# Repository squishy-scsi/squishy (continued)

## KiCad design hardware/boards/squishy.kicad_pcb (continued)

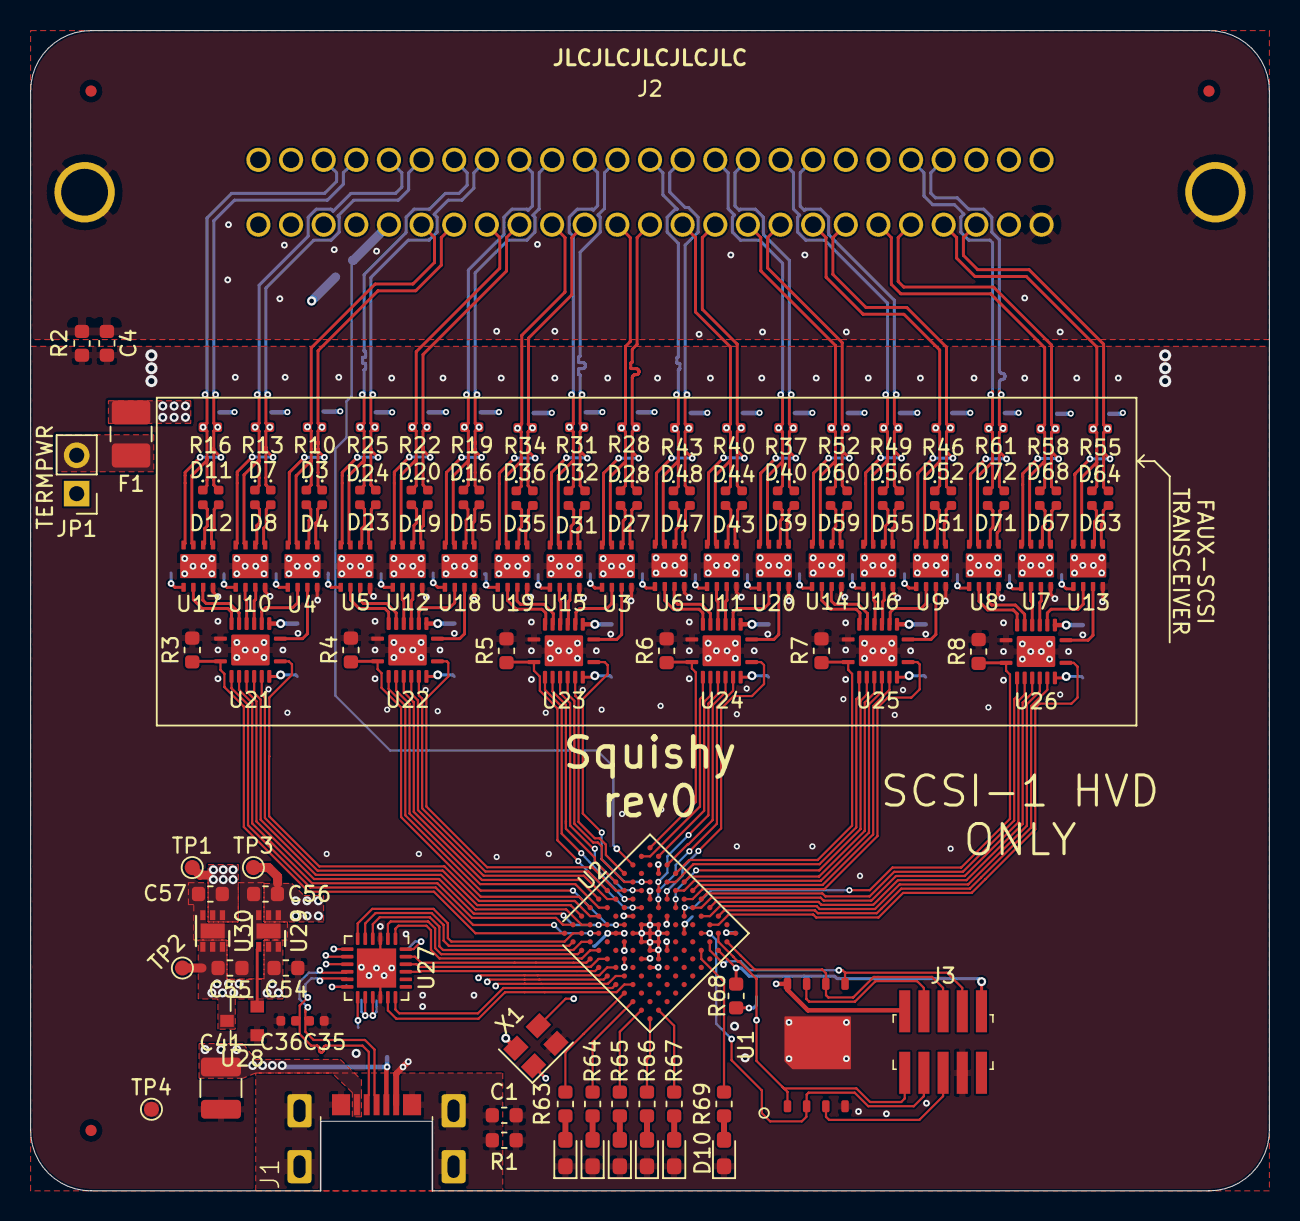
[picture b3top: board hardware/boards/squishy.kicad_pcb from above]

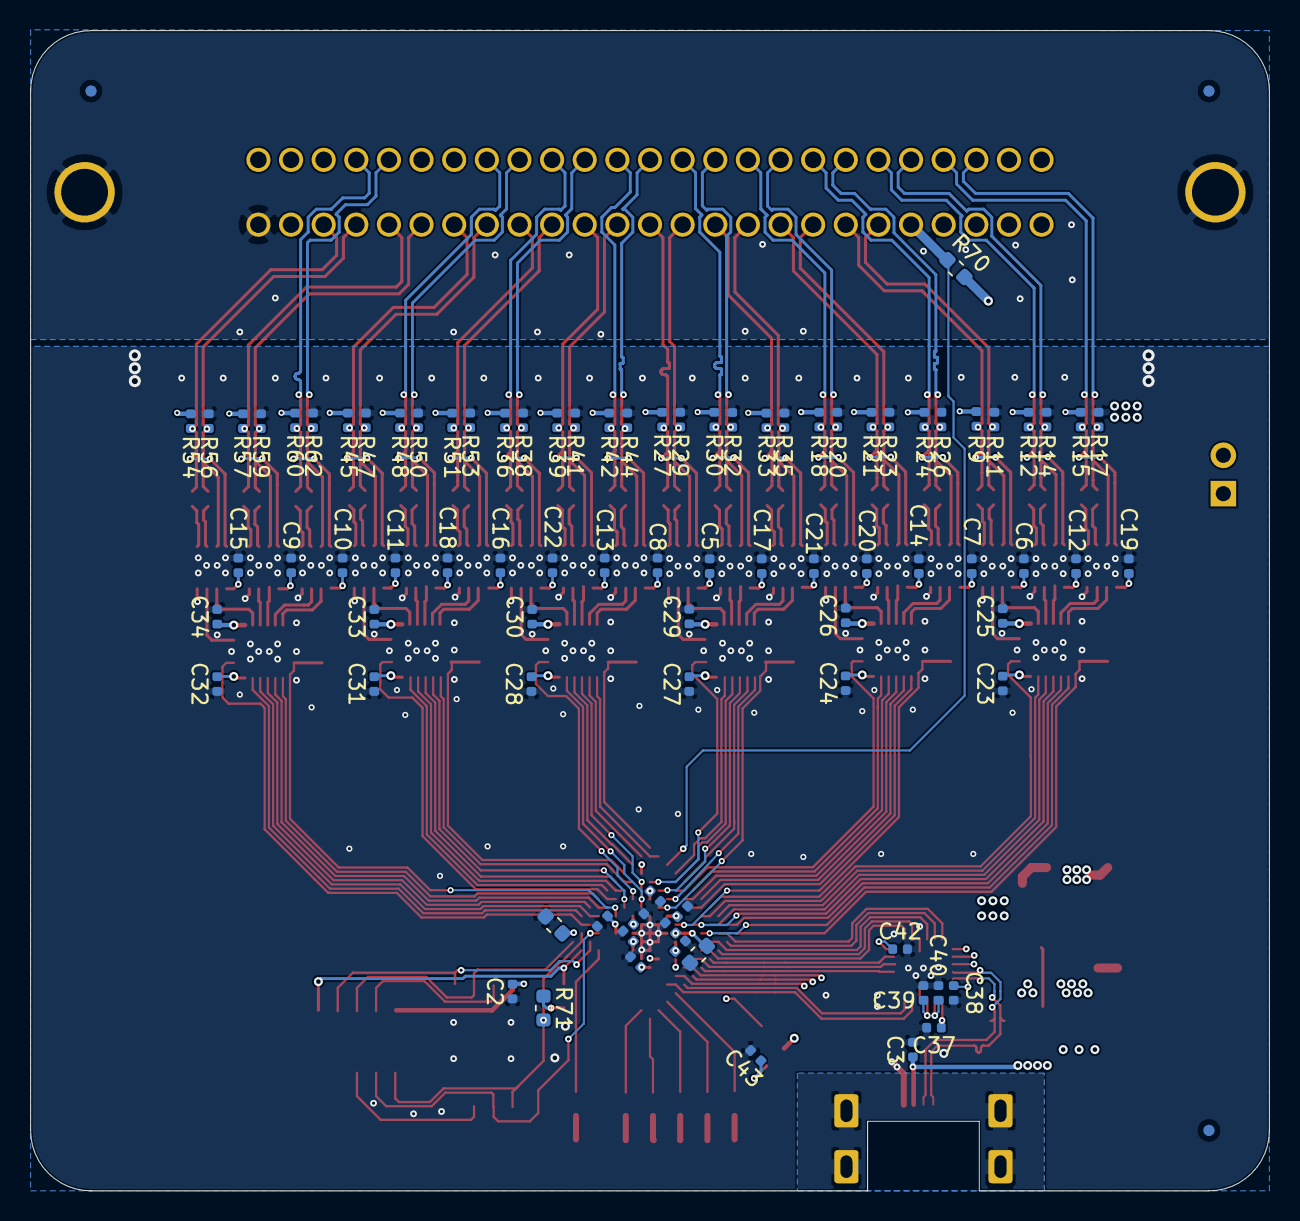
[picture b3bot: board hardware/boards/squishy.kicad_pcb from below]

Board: 4 copper layers, 82.0 x 76.8 mm, 216 parts (89 on the bottom side), 196 nets.

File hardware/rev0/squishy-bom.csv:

Reference,Quantity,Value,Datasheet,MFR,MPN
C1 C4,2,0.1uF,~,KEMET,C0603C104M5RACTU
C18 C17 C12 C6 C20 C14 C8 C22 C16 C10 C11 C5 C19 C13 C7 C21 C15 C9 C24 C26 C23 C25 C28 C30 C27 C29 C32 C34 C31 C33 C2 C42 C37 C38 C39 C40 C48 C50 C52 C46 C49 C51 C53 C47,44,0.1uF,~,KEMET,C0402C104M8PACTU
C3 C43,2,0.01uF,~,KEMET,C0402C103K3RACTU
C35 C36,2,47pf,~,KEMET,C0402C470K5GACTU
C41,1,100uF,~,KEMET,C1210C107M4PAC7800
C44 C45 C56 C54 C57 C55,6,4.7uF,~,KEMET,C0603C475K8PACTU
D1 D9 D10,3,BLUE,~,Wurth Electronics,150060BS75000
D2 D6,2,PINK,~,Optosupply,OSK40603C1E
D35 D36 D59 D60 D11 D12 D15 D16 D19 D20 D31 D32 D55 D56 D7 D8 D63 D64 D43 D44 D23 D24 D47 D48 D51 D52 D27 D28 D3 D4 D72 D71 D68 D67 D40 D39,36,D_Schottky_Small,https://www.comchiptech.com/admin/files/product/CDBQR0230L-H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,Comchip,CDBQR0230L-HF
D5,1,WHITE,~,ROHM Semiconductor,SMLEN3WBC8W1
F1,1,Polyfuse_Small,~,Bel Fuse,0ZCH0050FF2G
J1,1,USB_B_Micro,https://cdn.amphenol-icc.com/media/wysiwyg/files/drawing/101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,Amphenol ICC,10103593-0001lf
J2,1,Conn_02x26_Top_Bottom,https://content.norcomp.net/rohspdfs/SCSI-050Ribbon/11Y/112/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,NorComp,112-050-113R001
J3,1,Conn_02x05_Odd_Even,~,Samtec,FTSH-105-01-L-DV-K-TR
R1 R2,2,1M,~,Vishay Dale,CRCW06031M00FKEA
R4 R3 R6 R5 R8 R7 R66 R64 R70 R71 R68,11,10k,~,Vishay Dale,CRCW060310K0FKEA
R45 R47 R48 R50 R51 R53 R54 R56 R57 R59 R60 R62 R27 R29 R30 R32 R33 R35 R36 R38 R39 R41 R42 R44 R9 R11 R12 R14 R15 R17 R18 R20 R21 R23 R24 R26,36,330,~,TE Connectivity Passive Product ,CRGCQ0402F330R
R46 R49 R52 R55 R58 R61 R28 R31 R34 R37 R40 R43 R10 R13 R16 R19 R22 R25,18,150,~,TE Connectivity Passive Product ,CRGCQ0402F150R
R65,1,6k8,~,Vishay Dale,CRCW06036K80FKEA
R67 R63 R69,3,4k7,~,Vishay Dale,CRCW06034K70FKEA
U1,1,128MiB,https://www.winbond.com/resource-files/w25n01gv%20revl%20050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,Winbond,W25N01GVZEIG TR
U2,1,ICE40HX8K-BG121,http://www.latticesemi.com/Products/FPGAandCPLD/iCE40,Lattice Semiconductors,ICE40HX8K-BG121
U22 U21 U24 U23 U26 U25,6,TXB0106,https://www.ti.com/lit/ds/symlink/txb0106.pdf?HQS=TI-null-nu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,Texas Instruments,TXB0106RGYR
U27,1,FT240XQ,https://www.ftdichip.com/Support/Documents/DataSheets/ICs/DS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,FTDI,FT240XQ-R
U28,1,MAX809JTRG,https://www.mouser.com/datasheet/2/308/MAX809S-D-1811035.pdf,ON Semiconductors,MAX809JTRG
U29,1,TLV755533PDRVR,http://www.ti.com/lit/ds/symlink/tlv733p-q1.pdf,Texas Instruments,TLV75533PDRVR
U30,1,TLV73312PQDRVRQ1,http://www.ti.com/lit/ds/symlink/tlv755p.pdf,Texas Instruments,TLV73312PQDRVRQ1
U4 U7 U6 U13 U8 U19 U5 U11 U17 U3 U9 U15 U14 U20 U12 U18 U10 U16,18,THVD1451,https://www.ti.com/lit/ds/symlink/thvd1410.pdf?HQS=TI-null-n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,Texas Instruments,THVD1451DRBR
X1,1,ASEM-48MHz,http://abracon.com/Oscillators/ASEMB.pdf,Abracon,ASEMB-48.000MHZ-LY-T

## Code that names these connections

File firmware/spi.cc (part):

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	PORTA.set_output(pin::PSRAM_CS);

	/* Set up FPGA SPI Bus */
	PORTA.set_high(pin::FPGA_CS);
	PORTA.set_output(pin::FPGA_CS);

	PORTA.set_low(pin::FPGA_CLK);
	PORTA.set_output(pin::FPGA_CLK);

	PORTA.set_low(pin::FPGA_COPI);
	PORTA.set_output(pin::FPGA_COPI);
	PORTA.setup_pin(pin::FPGA_CIPO, false, true, false, false, port_t::pin_func_t::A);
	PORTA.set_input(pin::FPGA_CIPO);
}

static void setup_flash_pins() noexcept {
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static void fpga_begin_cmd(const fpga_cmd_t command) noexcept {
	const auto cmd{static_cast<std::uint8_t>(command)};

	PORTA.set_low(pin::FPGA_CS);

	[[maybe_unused]]
	auto _{fpga_xfr(cmd)};
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
static void fpga_cmd_run(const fpga_cmd_t command) noexcept {
	fpga_begin_cmd(command);
	PORTA.set_high(pin::FPGA_CS);
}

static void fpga_cmd_read(const fpga_cmd_t command, std::span<std::uint8_t> data) noexcept {
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		byte = fpga_xfr();
	}

	PORTA.set_high(pin::FPGA_CS);
}

static void fpga_cmd_write(const fpga_cmd_t command, const std::span<std::uint8_t>& data) noexcept {
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		auto _{fpga_xfr(byte)};
	}

	PORTA.set_high(pin::FPGA_CS);
}


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	for (std::size_t bit{}; bit < 8U; ++bit) {
		PORTA.set_low(pin::FPGA_CLK);

		PORTA.set_value((data >> (7U - bit)) & 0b1, pin::FPGA_COPI);

		/* High tech delay */
		asm (R"(
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
		PORTA.set_high(pin::FPGA_CLK);

		res |= std::uint8_t(PORTA.pin_state(pin::FPGA_CIPO) << (7U - bit));
	}

	PORTA.set_low(pin::FPGA_CLK);
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	for (std::size_t bit{}; bit < 8U; ++bit) {
		PORTA.set_low(pin::FPGA_CLK);

		PORTA.set_value((data >> bit) & 0b1, pin::FPGA_COPI);

		/* High tech delay */
		asm (R"(
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
		PORTA.set_high(pin::FPGA_CLK);

		res |= std::uint8_t(PORTA.pin_state(pin::FPGA_CIPO) << bit);
	}

	PORTA.set_low(pin::FPGA_CLK);
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		return false;
	}

	if (!PORTA.pin_state(pin::FPGA_INIT)) {
		active_fault = fault_code_t::FPGA_CFG_FAILED;
		return false;
	}
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
	/* Ensure the FPGA is released from the hold */
	PORTA.set_high(pin::FPGA_HOLD);
	PORTA.set_low(pin::FPGA_CS);

	if (!fpga_program_status() ) {
		return false;
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
	fpga_cmd_run(fpga_cmd_t::DISABLE);

	if (!PORTA.pin_state(pin::FPGA_DONE)) {
		active_fault = fault_code_t::FPGA_CFG_FAILED;
		return false;
	}
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	const auto bit_len{slot_header.bitstream_len()};

	/* Check if the FPGA is in configuration mode, if not, bail */
	if (PORTA.pin_state(pin::FPGA_DONE) || !PORTA.pin_state(pin::FPGA_INIT)) {
		active_fault = fault_code_t::FPGA_CFG_INVALID;
		return false;
	}
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
	};

	PORTA.set_high(pin::FPGA_CS);

	if (!fpga_program_status() ) {
		return false;
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
	fpga_cmd_run(fpga_cmd_t::DISABLE);

	if (!PORTA.pin_state(pin::FPGA_DONE)) {
		active_fault = fault_code_t::FPGA_CFG_FAILED;
		return false;
	}
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[[nodiscard]]
std::uint8_t read_squishy_register(const std::uint8_t addr) noexcept {

	PORTA.set_low(pin::FPGA_CS);
	[[maybe_unused]]
	auto _{gateware_xfr(addr)};

	const auto val{gateware_xfr(0U)};

	PORTA.set_high(pin::FPGA_CS);

	return val;
}

void write_squishy_register(const std::uint8_t addr, const std::uint8_t val) noexcept {
	PORTA.set_low(pin::FPGA_CS);

	[[maybe_unused]]
	auto _{gateware_xfr(addr)};
	_ = gateware_xfr(val);

	PORTA.set_high(pin::FPGA_CS);
}

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
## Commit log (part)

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2024-10-25 firmware: peripherals: Stubbed out `SYSCTRL` register block
2024-10-25 firmware: memory: Added memory header so we can call `memcpy` et. al.
2024-10-25 firmware: renamed `load_bitstream` to `load_bitstream_flash`
2024-10-25 firmware: spi: Added `fpga_segmented_xfer` to allow for fragmented bitstream loading from PSRAM to FPGA
2024-10-29 firmware: Added a *really* rough readme for building the firmware
2024-11-10 docs: Created connector and pinout diagrams and tables
2024-11-10 docs: pinouts: updated sources list to include direct links to the HD50/HD68 and added the CE50
2024-11-10 docs: pinouts: De-duplicated the SCSI-3 68-pin pinout tables
2024-11-10 docs: pinouts: Updated the scsi-se-50 pinout file
2024-11-10 docs: pinouts: Added the scsi-hvd-68 pinout file
2024-11-10 docs: pinouts: Added the scsi-lvd-68 pinout file
2024-11-18 squishy: gateware: peripherals: Updated SPI Flash peripheral.
    Updated the SPI Flash controller peripheral to use the new SPIController interface, meaning we no longer pass the resource down, we now manually extract the needed subsignals to construct the control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
    NOTE: There is some weirdness with the tests that was fixed by reaching into the SPI controller for it's Bus signals rather than using the global record signals, this reeks of unsoundness, and needs 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
2024-11-18 squishy: gateware: peripherals: Added SPI Interface
    Added a `SPIInterface` module that allows for a single SPI bus resource to be used as both a `SPIController` and/or a `SPIPeripheral` depending on the `SPIInterfaceMode` flag option.
    This is mainly useful for the rev2 platform where we need to act as a peripheral to the supervisor and a controller to the PSRAM that are both on the same SPI bus
2024-11-19 tests: gateware: peripheral: stubbed out the DUT and the test runner for the SPIPeripheral tests
2024-11-19 squishy: gateware: bootloader: started filling in the bits for the Rev2 bootloader
2024-11-20 setup: Bumped Torii version to 0.7.1 as the minimal required version
2024-11-22 squishy: gateware: peripherals: Started de-coupling the SPI XFR from the clock
2024-11-22 tests: gateware: peripherals: Started adding the CPOL Low tests and slowly working the kinks out
2024-11-28 tests: gateware: peripherals: fixed the SPI tests
2024-11-29 gateware: peripherals: spi: Fixed the SPIPeripheral and also filled out the tests
2024-11-29 gateware: peripherals: psram: Started implementing PSRAM read
2024-12-01 gateware: peripherals: psram: actually implemented the `ready` signal, oops
2024-12-01 ci: Updated python version 3.14 and also ensured that if the 3.14 test fails it's okay
2024-12-01 test: peripherals: psram: shrunk the PSRAM data test if we are running in CI so we don't take literally forever
2024-12-03 gateware: bootloader: Removed the unneeded extra addition of the `StallOnlyRequestHandler` as that is built by SOL on-the-fly from handler conditions.
    This also resolved the issue where the bootloader module when provided with the same synth options would fail cache lookup, because the SOL request handler name disambiguation would kick in, this mig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
2024-12-12 core/contrib: Almost fully re-wrote the pcapng generator to make it less awful
2024-12-14 gateware: peripherals: spi: Fixed an potential edge case where CS may drop if we are in the middle of our state machine, causing a de-sync
2024-12-14 gateware: actions: run_synth: was silly and mixed up `>` and `<` again, so it was setting random seed if you ever specified a non-zero PnR seed
2024-12-14 gateware: bootloader: rev2: Actually stuck the SPIPSRAM block into the bootloader for use (RIP our timings, but I guess 175MHz isn't /too/ bad)
2024-12-17 gateware: bootloader: rev2: removed unended aliases for SPI controller and peripheral
2024-12-18 docs: minor updates
2024-12-18 actions: Added a little more info for when the bitstream cache is hit and we're using that
2024-12-18 core/applets: Added initial `LINKTYPE_PARALLEL_SCSI` bits
2024-12-18 core: pcapng: got rid of `if __name__ == '__main__'` from the bottom of the pcapng module that was being used for testing
2024-12-18 tests: gateware: bootloader: fixed test class name for the rev1 bootloader tests
2024-12-18 gateware: platform: Added a "proper" resource for the banked HyperRAM
2024-12-19 gateware: platform: Added a proper resource for the Squishy Supervisor bus
2024-12-19 gateware: platform: resources: Added a fairly rough raw SCSI bus resource
2024-12-23 gateware: core: supervisor_csr: added IRQ reasons to the IRQ register
2024-12-23 gateware: bootloader: rev2: Updated the bootloader protocol docs
2024-12-24 gateware: usb: dfu: Fixed the DFU state change in `HANDLE_DOWNLOAD_COMPLETE` state, it was AppIdle, should have been DFUIdle
2024-12-24 gateware: bootloader: hooked up the extra dl_completed signal from the DFU handler to the bootloader bits, except in the rev1 bootloader integration tests, as that signal is currently unused in that 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
2024-12-24 gateware: bootloader: rev2: fix the slot change timing so we actually latch the slot, and not just 0
2024-12-24 tests: gateware: boot: rev2: Added the Supervisor side of the integration test
2024-12-25 gateware: bootloader: rev2: fixed PSRAM clock polarity
2024-12-25 tests: gateware: boot: rev2: Added gating for the DFU data generation so CI doesn't take literally hours
2024-12-25 noxfile: Added `-v` to the unit test runner so we know where we are test wise
2024-12-26 core: flash: Fixed up the Squishy rev2 flash image bits in preparation for artifact packing
2024-12-27 gateware: bootloader: fixed the DFU interface,
    Still doesn't work, but hey,
2025-01-03 noxfile: ensure the `test` session uses system site packages to speed up venv install and setup
2025-01-04 firmware: started setting up EIC support for the FPGA <-> Supervisor comms
2025-01-05 tests: gateware: bootloader: fixed the weirdness with the helper mixin
2025-01-05 support: tests: made `usb_ack` match `usb_(get/send)_zlp`
2025-01-05 support: tests: added a `usb_set_interface` helper
2025-01-05 support: tests: added `crc16_buff` so we can compute the crc16 of arbitrary data buffers
2025-01-05 support: test: Reduced the timeouts for achieving various states on D+/D-
2025-01-05 tests: gateware: bootloader: Added a `dfu_get_status()` helper
2025-01-05 tests: gateware: bootloader: Simulated getting a couple of the string descriptors, the current device configuration, and the MS OS descriptor
2025-01-06 deps: bumped minimum SOL version to 0.4.1, removed `usb-construct` as it is a transitive dependency of SOL
2025-01-07 gateware: platform: resources: forgot to stage the resource itself, oops
2025-01-08 firmware: fault: Fixed an arithmetic conversion
2025-01-08 firmware: startup: Ensured we disable the EIC when we fall into `std::terminate`
2025-01-08 firmware: Moved the green LED blink wiggles into the systick handler
2025-01-08 firmware: spi: Added a rough impl of `read_squishy_register`
2025-01-08 firmware: spi: Added Squishy register address constants
2025-01-08 firmware: fpga: Added slot constants to try to get rid of magic numbers
2025-01-09 firmware: fpga: Added handling for the `WANT DFU` IRQ from the FPGA
2025-01-09 gateware: fixed some comment typos
2025-01-10 firmware: spi: fixed the FPGA ID check to allow for both the 5G and non-5G variants
2025-01-10 firmware: spi: rough `move_to_slot` impl
2025-01-10 firmware: fpga: added the last little bit of the FPGA boot protocol handling
2025-01-12 gateware: peripherals: spi: Fixed and oopsie that causes us to hold the shared SPI bus hostage, even when we're a peripheral
2025-01-12 firmware: peripherals: Added new NVIC priority `MID`
2025-01-12 firmware: main: enabled the pulldown on the `SU_ATTN` line to prevent spurious triggers
2025-01-12 firmware: main: Fixed the interrupt numbers in the `EIC` interrupt number check
2025-01-12 gateware: bootloader: rev2: Fixed a case where the DFU machinery would ask for a reboot but the controller would just be stuck in IDLE
2025-01-12 gateware: platform: rev2: Fixed a bug where despite everything CIPO and COPI are backwards on the supervisor SPI interface???
2025-01-13 gateware: peripherals: spi: Fixed a bug where CIPO was set up a bit too late in the SPI Peripheral
2025-01-15 support: test: Removed dead exports from `__all__`
2025-01-15 tests: gateware: usb: Fixed the sync domain leaking into the duf and windows USB request handler tests
2025-01-15 firmware: spi: Ensure we write the first SPI buffer page we read once we know it's valid
2025-01-15 gateware: bootloader: rev2: Added a delay slot for re-timing the `SLOT_CHANGED` signal so we hopefully latch it correctly
2025-01-19 noxfile/ci: Automatically enable test coverage if in CI, or if `SQUISHY_TEST_COVERAGE` env var is set
2025-01-19 noxfile: re-organized imports
2025-01-19 contrib: Updated squishy udev rules
2025-01-19 gateware: peripherals: psram: Added a 10-cycle wait to the SPI CS transitions.
    This is due to the NOR gate on the PSRAM CS line, if we try to wiggle the CS and then blast data into it's face as fast as we want we have some timing violations to contend with.
2025-01-20 squishy: actions: Added/Cleaned up some module docs
2025-01-20 test: gateware: peripherals: psram: fixed the psram_read test
2025-01-20 core: cache: Added some module docs
2025-01-20 core: flash: Added module docs
2025-01-23 firmware: spi: Disabled PSRAM SPI test due to squishy-scsi/hardware#17
2025-02-08 ci: s/Torii/Squishy/
2025-02-08 ci: fixed meson setup line to actually use the Firmware directory
2025-02-08 setup: Updated trove classifiers
2025-02-08 squishy: Suffixed `python` with `3` on the shebang line
2025-03-07 tests: Fixed deprecated `DIR_*` usage
2025-03-10 ci: Fixed docs artifact upload
2025-03-11 deps: Replaced SOL with torii_usb
2025-03-11 docs: Added autodoc typehints
2025-03-16 docs: Updated contribution guidelines
2025-03-25 docs: Fixed syntax highting for dark/light themes
2025-03-25 docs: cleaned up styles
2025-05-16 docs: Fixed CC-BY-SA links
2025-06-24 contrib: Updated `coveragerc` file
2025-07-21 build; Replaced `setup.py` with `pyproject.toml`
2025-07-21 noxfile: Refactored noxfile
2025-07-21 ci: Updated workflow
2025-07-26 squishy: Cleaned up imports
2025-07-26 squishy.applets: Cleaned up imports
2025-07-26 gateware.peripherals: Cleaned up imports
2025-07-26 gateware.bootloader: Cleaned up imports
2025-07-26 squishy.scsi.commands: Cleaned up imports
2025-07-26 gateware.usb: Cleaned up imports
2025-07-26 squishy: Removed explicit version check
    We only support Python 3.11 and newer, so we had a check in `__init__` that would fail if ran by an older version of python.
    But, that's not super useful anymore I suppose
2025-07-26 tests.usb: Cleaned up imports
2025-07-26 docs: cleaned up imports
2025-07-29 git: Updated `.gitattributes` and `.gitignore`
2025-08-02 misc: Fixed up flake8 rules
2025-08-03 docs: Fixed formatting lints
2025-08-03 squishy.actions: Fixed formatting lints
2025-08-03 squishy.core: Fixed formatting lints
2025-08-03 squishy.gateware.applet: Fixed formatting lints
2025-08-03 squishy.gateware.peripherals: Fixed formatting lints
2025-08-03 squishy.gateware.usb: Fixed formatting lints
2025-08-03 squishy.scsi.commands: Fixed formatting lints
2025-08-03 squishy.support.test: Fixed formatting lints
2025-08-03 tests.gateware.usb.quirks: Fixed formatting lints
2025-08-06 squishy.scsi.vid: Fixed up formatting of VID mapping
2025-08-08 misc: Removed the icons that were unused
2025-08-08 docs: Updated license page
2025-08-08 docs: Cleaned up formatting
2025-08-12 misc: Fixed license file name
2025-09-14 squishy.gateware: Fixed imports for USB construct and `torii_usb`
2025-10-14 ci: Python 3.14 released, move to required CI version
    Once Python 3.15-dev is added to `actions/setup-python` we'll add that as an optional Python version
